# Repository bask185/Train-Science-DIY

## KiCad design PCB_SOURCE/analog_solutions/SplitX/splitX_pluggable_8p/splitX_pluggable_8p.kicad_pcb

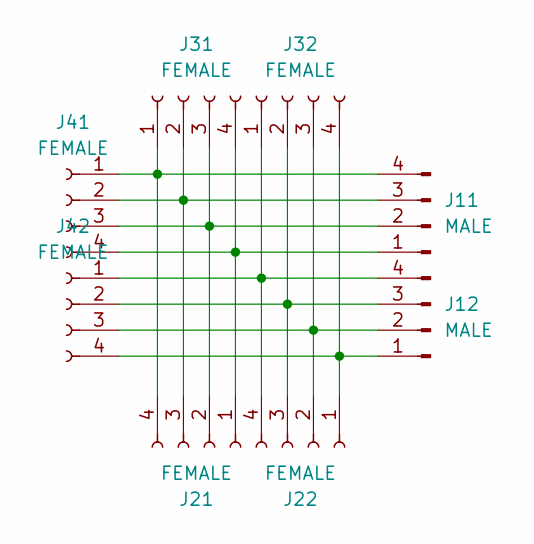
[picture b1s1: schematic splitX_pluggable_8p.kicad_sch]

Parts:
J11, J12: MALE; connector_3.50mm_4P horizontal_MALE
J21, J22, J31, J32, J41, J42: FEMALE; PhoenixContact_MC_1,5_4-G-3.5_1x04_P3.50mm_Horizontal

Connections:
unnamed: J11.1, J21.1, J31.4, J41.4
unnamed: J11.2, J21.2, J31.3, J41.3
unnamed: J11.3, J21.3, J31.2, J41.2
unnamed: J11.4, J21.4, J31.1, J41.1
unnamed: J12.1, J22.1, J32.4, J42.4
unnamed: J12.2, J22.2, J32.3, J42.3
unnamed: J12.3, J22.3, J32.2, J42.2
unnamed: J12.4, J22.4, J32.1, J42.1

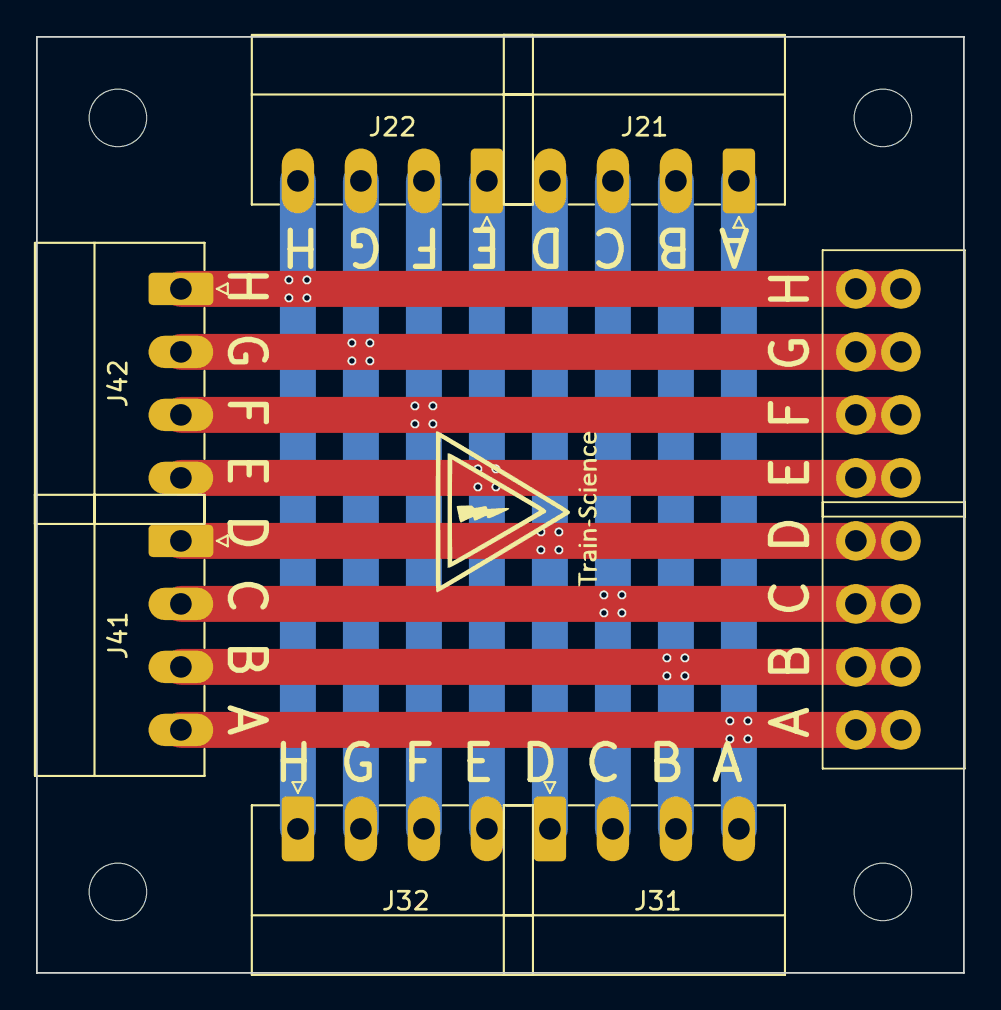
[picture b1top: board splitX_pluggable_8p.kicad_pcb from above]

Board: 2 copper layers, 51.5 x 52.0 mm, 8 parts (0 on the bottom side), 8 nets.

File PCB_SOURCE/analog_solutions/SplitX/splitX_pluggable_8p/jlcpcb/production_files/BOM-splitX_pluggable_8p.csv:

Comment,Designator,Footprint,LCSC
FEMALE,J42,"PhoenixContact_MC_1,5_4-G-3.5_1x04_P3.50mm_Horizontal",
FEMALE,J21,"PhoenixContact_MC_1,5_4-G-3.5_1x04_P3.50mm_Horizontal",
FEMALE,J31,"PhoenixContact_MC_1,5_4-G-3.5_1x04_P3.50mm_Horizontal",
FEMALE,J32,"PhoenixContact_MC_1,5_4-G-3.5_1x04_P3.50mm_Horizontal",
MALE,J11,connector_3.50mm_4P horizontal_MALE,
FEMALE,J22,"PhoenixContact_MC_1,5_4-G-3.5_1x04_P3.50mm_Horizontal",
MALE,J12,connector_3.50mm_4P horizontal_MALE,
FEMALE,J41,"PhoenixContact_MC_1,5_4-G-3.5_1x04_P3.50mm_Horizontal",

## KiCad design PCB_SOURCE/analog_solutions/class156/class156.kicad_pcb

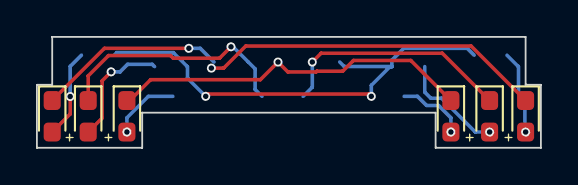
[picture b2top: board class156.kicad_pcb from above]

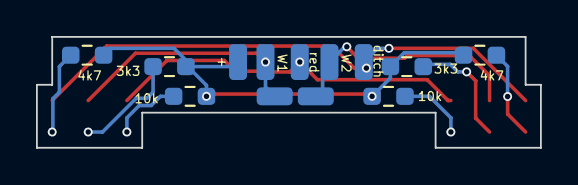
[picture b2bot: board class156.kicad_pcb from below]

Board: 2 copper layers, 28.0 x 6.2 mm, 19 parts (13 on the bottom side), 11 nets.

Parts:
D1, D2, D3, D4, D5, D6: LED; LED_0603_1608Metric_Pad1.05x0.95mm_HandSolder
J1: ditch; SolderWirePad_1x01_SMD_1x2mm
J2, J6: W1; SolderWirePad_1x01_SMD_1x2mm
J3: red; SolderWirePad_1x01_SMD_1x2mm
J4: Conn_01x01_Pin; SolderWirePad_1x01_SMD_1x2mm
J5, J7: W3; SolderWirePad_1x01_SMD_1x2mm
R1, R6: 4k7; R_0603_smalltext
R2, R5: 3k3; R_0603_smalltext
R3, R4: 10k; R_0603_smalltext

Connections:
unnamed: D1.2 (A), R1.2
unnamed: D1.1 (K), D6.1 (K), J1.1
unnamed: D2.2 (A), R2.2
unnamed: D2.1 (K), J2.1, J6.1
unnamed: D3.2 (A), R3.2
unnamed: D3.1 (K), D4.1 (K), J3.1
unnamed: D4.2 (A), R4.2
unnamed: D5.2 (A), R5.2
unnamed: D5.1 (K), J5.1, J7.1
unnamed: D6.2 (A), R6.2
VCC: J4.1, R1.1, R2.1, R3.1, R4.1, R5.1, R6.1

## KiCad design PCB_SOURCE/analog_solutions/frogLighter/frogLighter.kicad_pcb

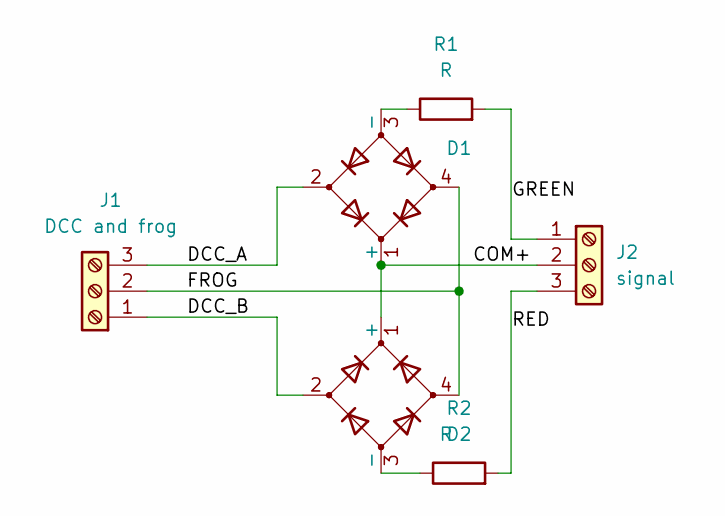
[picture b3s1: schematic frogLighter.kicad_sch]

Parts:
D1, D2: D_Bridge_+A-A; Diode_Bridge_Round_D9.0mm
J1: DCC and frog; TerminalBlock_Phoenix_MKDS-1,5-3-5.08_1x03_P5.08mm_Horizont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
J2: signal; TerminalBlock_Phoenix_MKDS-1,5-3-5.08_1x03_P5.08mm_Horizont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
R1, R2: R; R_Axial_DIN0204_L3.6mm_D1.6mm_P7.62mm_Horizontal

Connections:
/COM+: D1.1 (+), D2.1 (+), J2.2
/DCC_A: D1.2, J1.3
/DCC_B: D2.2, J1.1
/FROG: D1.4, D2.4, J1.2
/GREEN: J2.1, R1.2
/RED: J2.3, R2.2
unnamed: D1.3 (-), R1.1
unnamed: D2.3 (-), R2.1

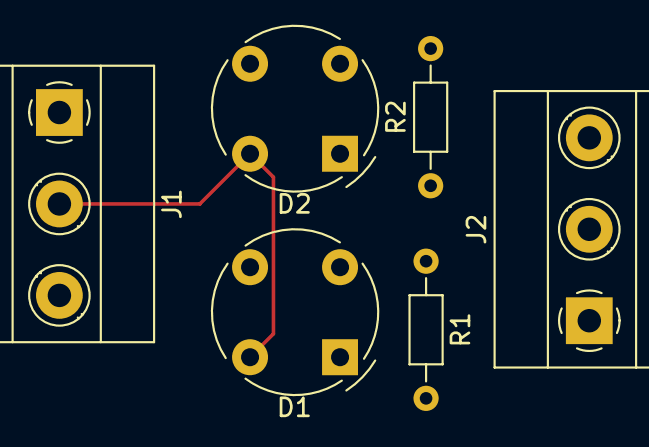
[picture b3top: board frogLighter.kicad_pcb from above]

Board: 2 copper layers, 6 parts (0 on the bottom side), 8 nets.

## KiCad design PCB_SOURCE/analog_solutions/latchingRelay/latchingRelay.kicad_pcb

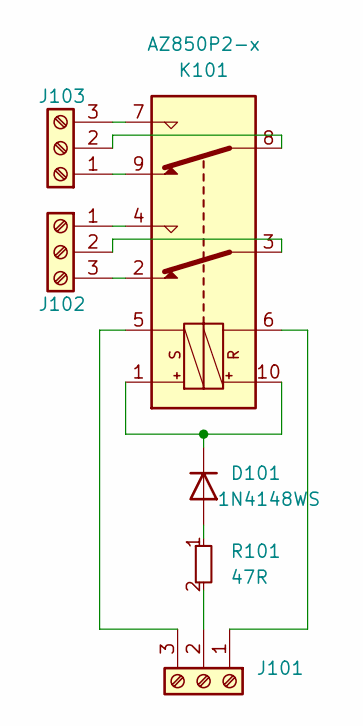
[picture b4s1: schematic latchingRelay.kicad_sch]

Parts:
D101: 1N4148WS; D_SOD-323; JLCPCB Part# C2128
J101, J102, J103: Screw_Terminal_01x03; PhoenixContact_MC_1,5_3-G-3.5_1x03_P3.50mm_Horizontal; JLCPCB Part# C880573
K101: AZ850P2-x; Relay_DPDT_FRT5
R101: 47R; R_0805_handsolder-smalltext; JLCPCB Part# C17714

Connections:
unnamed: D101.2 (A), R101.1
unnamed: D101.1 (K), K101.1, K101.10
unnamed: J101.1, K101.6
unnamed: J101.2, R101.2
unnamed: J101.3, K101.5
unnamed: J102.1, K101.4
unnamed: J102.2, K101.3
unnamed: J102.3, K101.2
unnamed: J103.1, K101.9
unnamed: J103.2, K101.8
unnamed: J103.3, K101.7

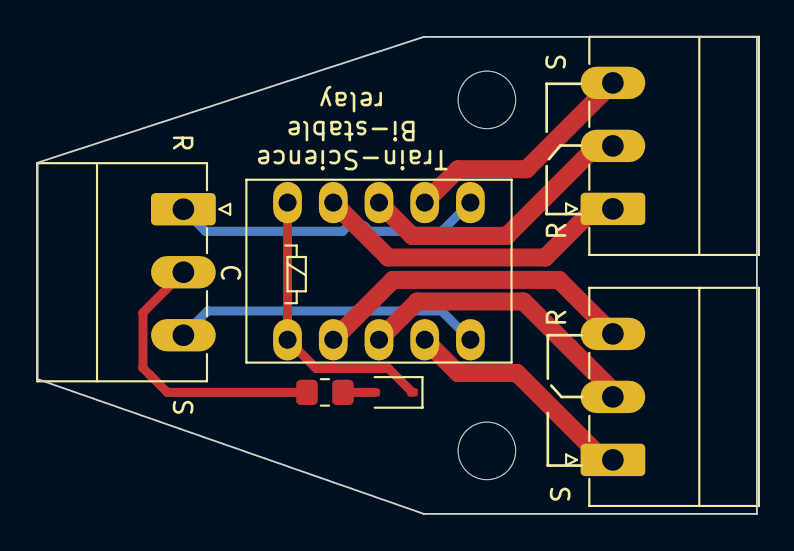
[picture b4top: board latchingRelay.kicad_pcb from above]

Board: 2 copper layers, 40.0 x 26.5 mm, 6 parts (0 on the bottom side), 11 nets.

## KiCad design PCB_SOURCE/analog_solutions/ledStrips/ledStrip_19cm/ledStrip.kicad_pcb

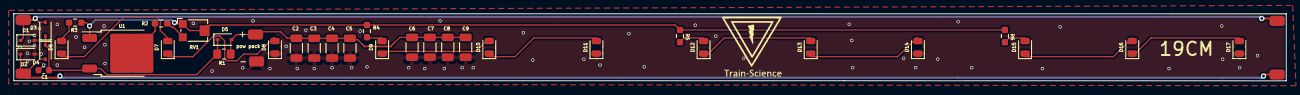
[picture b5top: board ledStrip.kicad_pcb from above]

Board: 2 copper layers, 190.0 x 10.0 mm, 35 parts (0 on the bottom side), 20 nets.

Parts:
AC2: (no value)
C1: 100nF; C_0603_1608Metric
C2, C3, C4, C5, C6, C7, C8, C9: 22uF; C_1206_3216Metric
D1, D2, D3, D4, D5: 1N4148WS; D_SOD-323
D6, D7, D8, D9, D10, D11, D12, D13, D14, D15, D16, D17: LED; LED_0805_2012Metric
R1: 100R; R_0805_handsolder-smalltext
R2: 100R; R_0603_smalltext
R3, R4, R5, R6: 10R; R_0603_smalltext
RV1: 500R; Potentiometer_Bourns_TC33X_Vertical
U1: LM317_TO-252; TO-252-2

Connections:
/Vled: R3.1, R4.1, R5.1, R6.1, RV1.1, RV1.2, U1.1 (ADJ)
AC1: D2.1 (K), D4.2 (A)
AC2: AC2.1, D1.1 (K), D3.2 (A)
GND: C1.2, C2.2, C3.2, C4.2, C5.2, C6.2, C7.2, C8.2, C9.2, D1.2 (A), D2.2 (A), D8.1 (K), D11.1 (K), D14.1 (K), D17.1 (K)
unnamed: C2.1, C3.1, C4.1, C5.1, C6.1, C7.1, C8.1, C9.1, D5.2 (A), R1.1
unnamed: D6.2 (A), R3.2
unnamed: D6.1 (K), D7.2 (A)
unnamed: D7.1 (K), D8.2 (A)
unnamed: D9.2 (A), R4.2
unnamed: D9.1 (K), D10.2 (A)
unnamed: D10.1 (K), D11.2 (A)
unnamed: D12.2 (A), R5.2
unnamed: D12.1 (K), D13.2 (A)
unnamed: D13.1 (K), D14.2 (A)
unnamed: D15.2 (A), R6.2
unnamed: D15.1 (K), D16.2 (A)
unnamed: D16.1 (K), D17.2 (A)
unnamed: R2.2, RV1.3
unnamed: R2.1, U1.2 (VO)
VCC: C1.1, D3.1 (K), D4.1 (K), D5.1 (K), R1.2, U1.3 (VI)
